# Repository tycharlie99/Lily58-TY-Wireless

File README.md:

# TsunyYu - Lily58

An ergonomic, split mechanical keyboard with a 58-key columnar-staggered layout, derived from the original [Lily58](https://github.com/kata0510/Lily58). This specific variant is optimized for wireless dual-mode connectivity and ultra-low-power Nice!View displays, perfect for developers and creators seeking a clean, cable-free workspace.

## Features

- **Ergonomic Columnar Layout**: 4x12 matrix with 5 thumb keys per side (58 keys total) reduces finger travel and hand strain.
- **Wireless-Ready**: Integrated battery support for seamless Bluetooth operation when paired with BLE controllers (e.g., nice!nano).
- **Nice!View Optimization**: Native compatibility with the low-power Sharp Memory Display (Nice!View), offering a high refresh rate with a fraction of the power consumption of traditional OLEDs.
- **Reversible PCB Design**: Uses a mirrored, flippable design for the left and right sides to simplify manufacturing and sourcing.
---

## Bill of Materials (BOM)

Below is the complete list of components required to build one full TsunyYu - Lily58 keyboard (including both left and right halves):

| Item | Quantity | Model/Specification / Notes |
| --- | --- | --- |
| **Lily58 PCB** | 2 | Left and right halves (reversible design) |
| **PCB Plate** | 2 | Left and right halves (compatible with 58-key layout) |
| **Microcontroller** | 2 | Pro Micro or compatible BLE wireless controllers (e.g., nice!nano) |
| **Display** | 2 | Nice!View (Ultra-low-power display; backward compatible with 0.91" OLED) |
| **Key Socket** | 58 | Kailh Hotswap Sockets |
| **Switches** | 58 | MX switches |
| **Keycaps** | 58 | 1U keycaps recommended, 1.5U optional for thumb keys |
| **Diodes** | 58 | 1N4148W (SOD-123) |
| **Resistors** | 4 | 4k7 ohm (0603) Used for I2C/Display signal stability |
| **TRRS Jack** | 2 | PJ-320A or equivalent (for wired connection between halves) |
| **Batteries** | 2 | 3.7V Li-Po batteries (Required for wireless; 110mAh to 300mAh recommended) |
| **Battery Holders** | 2 | JST GH 1.25mm 2p |
| **Reset Buttons** | 2 | KXT 321 |

---

## Hardware & Soldering Guide

Please review these critical steps before heating up your soldering iron:

1. **Orientation Check**: Because the PCB is reversible, make sure you clearly identify the "Left" and "Right" sides before soldering any components. Do not accidentally mirror the components on the same side.
2. **Diode Polarity**: Diodes are directional. Ensure the line on the diode (cathode) aligns with the thick line/bar indicated on the PCB silkscreen markings.
3. **Wireless Safety Precautions**:
   - Always unplug the battery from the **JST GH connector** before soldering/desoldering any components nearby to prevent accidental short circuits.
   - It is highly recommended to apply **insulating tape** (like Kapton tape) over the PCB traces beneath the microcontroller to prevent shorts between the controller pins and the PCB components/battery.
   - Pay close attention to the pinout when installing the Nice!View. It requires 5 pins (including a CS pin), differing slightly from standard 4-pin OLED setups.

---

## Firmware Support

This build is fully compatible with open-source keyboard firmwares:

- **ZMK Firmware (Highly Recommended)**: The ideal choice when paired with nice!nano controllers. It natively handles Bluetooth multi-device pairing and unlocks the full low-power efficiency of the Nice!View screen.
- **QMK Firmware**: Best suited for standard wired setups using traditional Pro Micro controllers.

---

## References & Credits

This project is built upon and inspired by the incredible open-source work of the mechanical keyboard community:

- [kata0510/Lily58](https://github.com/kata0510/Lily58) - The original Lily58 design.
- [ZMK Firmware](https://zmk.dev/) & [nice!nano](https://nicekeyboards.com/) - Providing the robust ecosystem for wireless split keyboards.

---

## License

This hardware project is open-source and distributed under the same licensing terms as the original repository:
- **Distributed under the [MIT License](LICENSE)** *(Or specify CERN OHL if applicable to your custom PCB modifications).*

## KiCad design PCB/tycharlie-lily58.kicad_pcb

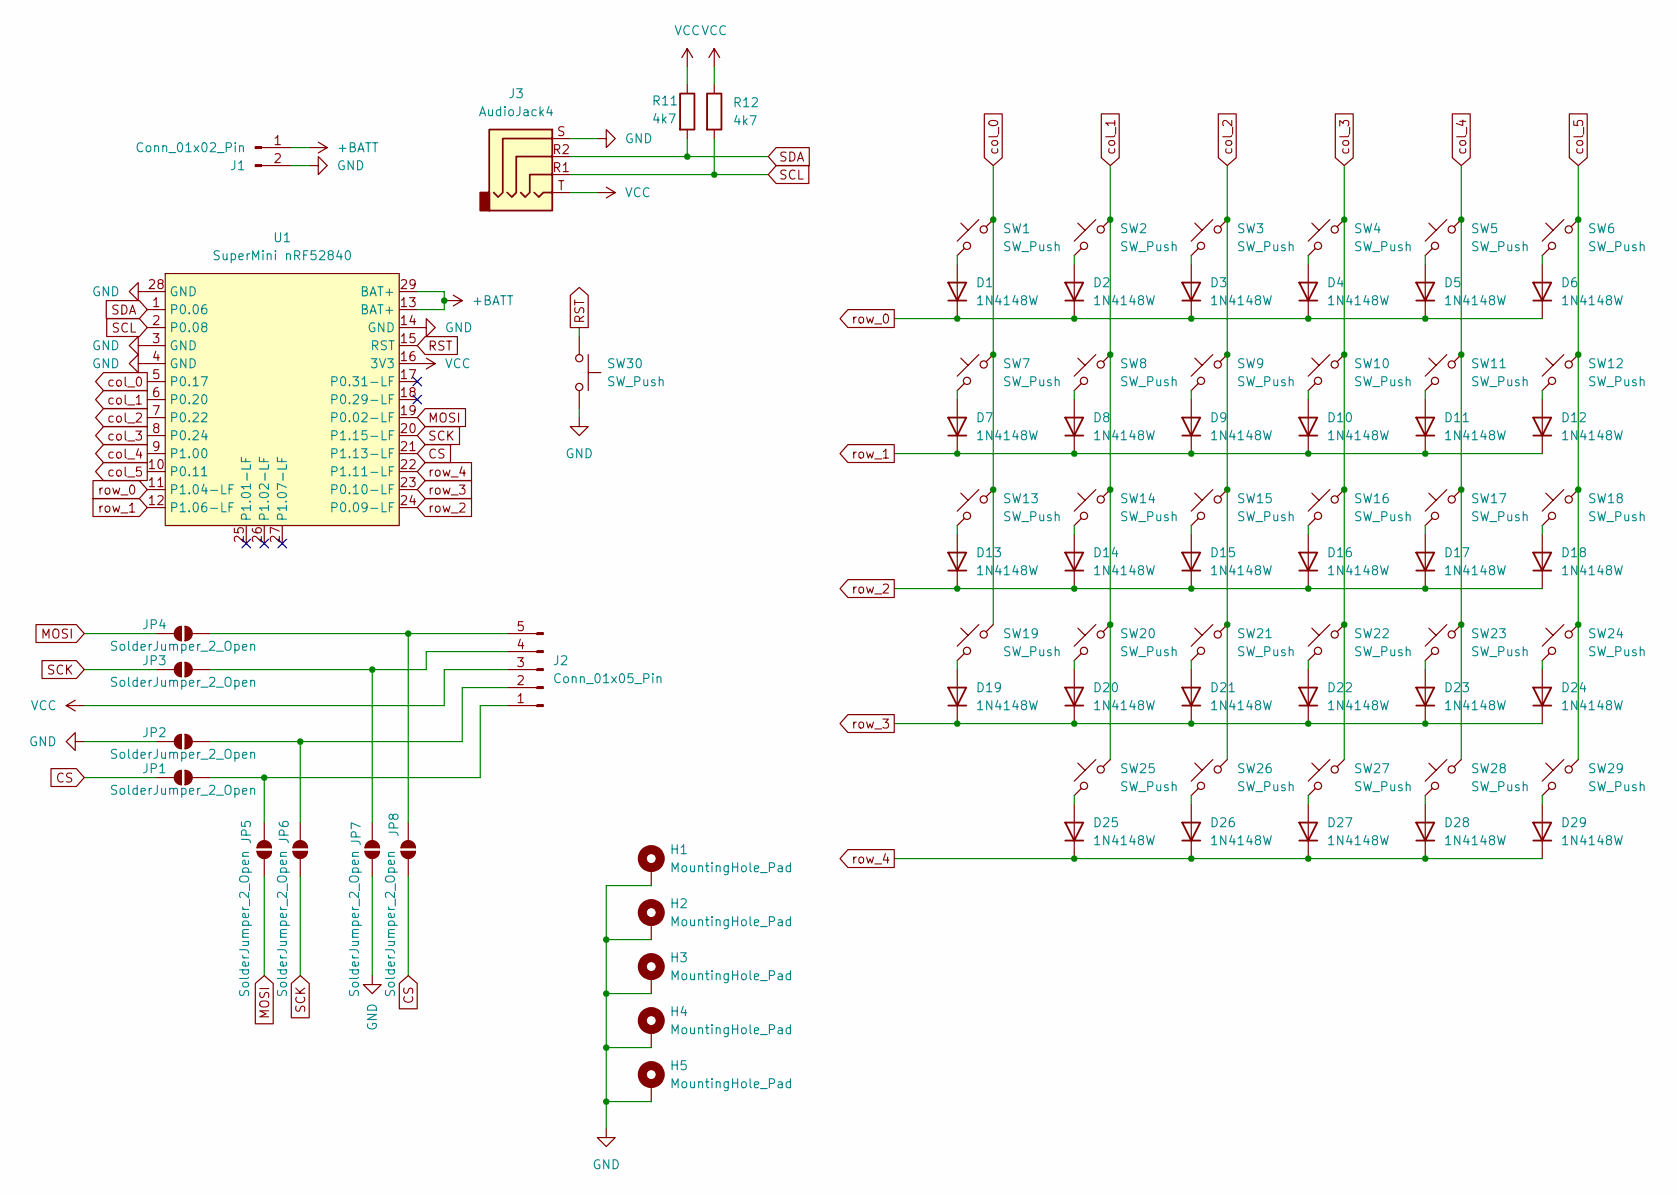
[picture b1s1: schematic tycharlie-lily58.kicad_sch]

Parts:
D1, D2, D3, D4, D5, D6, D7, D8, D9, D10, D11, D12, D13, D14, D15, D16, D17, D18, D19, D20, D21, D22, D23, D24, D25, D26, D27, D28, D29: 1N4148W; D_SOD-123
H1, H2, H4: MountingHole_Pad; MountingHole_3mm_Oval_Hole_ISO14580_Pad_TopBottom
H3: MountingHole_Pad; MountingHole_2.2mm_M2_ISO14580_Pad_TopBottom
H5: MountingHole_Pad; MountingHole_3mm_M2_ISO14580_Pad_TopBottom
J1: Conn_01x02_Pin; Molex_PicoBlade_53261-0271_1x02-1MP_P1.25mm_Horizontal
J2: Conn_01x05_Pin; PinHeader_1x05_P2.54mm_Vertical
J3: AudioJack4; CON_MJ-4PP-9_Reversible
JP1, JP2, JP3, JP4, JP5, JP6, JP7, JP8: SolderJumper_2_Open; SolderJumper-2_P1.3mm_Open_RoundedPad1.0x1.5mm
R11, R12: 4k7; R_0603_1608Metric_Pad0.98x0.95mm_HandSolder
SW1, SW2, SW3, SW4, SW5, SW6, SW7, SW8, SW9, SW10, SW11, SW12, SW13, SW14, SW15, SW16, SW17, SW18, SW19, SW20, SW21, SW22, SW23, SW24, SW25, SW26, SW27, SW29: SW_Push; SW_Hotswap_Reversible_Kailh_MX_Plated_1.00u
SW28: SW_Push; SW_Hotswap_Reversible_Kailh_MX_Plated_1.50u
SW30: SW_Push; SW_SPST_CK_KXT3
U1: SuperMini nRF52840; SuperMini_nRF52840_without_25-27

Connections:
+BATT: J1.1, U1.13 (BAT+), U1.29 (BAT+)
CS: JP1.1 (A), JP8.1 (A), U1.21 (P1.13-LF)
GND: H1.1 (1_1), H2.1 (1_1), H3.1 (1_1), H4.1 (1_1), H5.1 (1_1), J1.2, J3.S, JP2.1 (A), JP7.1 (A), SW30.2, U1.3 (GND), U1.4 (GND), U1.14 (GND), U1.28 (GND)
MOSI: JP4.1 (A), JP5.1 (A), U1.19 (P0.02-LF)
unnamed: D1.2 (A), SW1.1
unnamed: D2.2 (A), SW2.1
unnamed: D3.2 (A), SW3.1
unnamed: D4.2 (A), SW4.1
unnamed: D5.2 (A), SW5.1
unnamed: D6.2 (A), SW6.1
unnamed: D7.2 (A), SW7.1
unnamed: D8.2 (A), SW8.1
unnamed: D9.2 (A), SW9.1
unnamed: D10.2 (A), SW10.1
unnamed: D11.2 (A), SW11.1
unnamed: D12.2 (A), SW12.1
unnamed: D13.2 (A), SW13.1
unnamed: D14.2 (A), SW14.1
unnamed: D15.2 (A), SW15.1
unnamed: D16.2 (A), SW16.1
unnamed: D17.2 (A), SW17.1
unnamed: D18.2 (A), SW18.1
unnamed: D19.2 (A), SW19.1
unnamed: D20.2 (A), SW20.1
unnamed: D21.2 (A), SW21.1
unnamed: D22.2 (A), SW22.1
unnamed: D23.2 (A), SW23.1
unnamed: D24.2 (A), SW24.1
unnamed: D25.2 (A), SW25.1
unnamed: D26.2 (A), SW26.1
unnamed: D27.2 (A), SW27.1
unnamed: D28.2 (A), SW28.1
unnamed: D29.2 (A), SW29.1
unnamed: J2.1, JP1.2 (B), JP5.2 (B)
unnamed: J2.2, JP2.2 (B), JP6.2 (B)
unnamed: J2.4, JP3.2 (B), JP7.2 (B)
unnamed: J2.5, JP4.2 (B), JP8.2 (B)
RST: SW30.1, U1.15 (RST)
SCK: JP3.1 (A), JP6.1 (A), U1.20 (P1.15-LF)
SCL: J3.R1, R12.2, U1.2 (P0.08)
SDA: J3.R2, R11.2, U1.1 (P0.06)
VCC: J2.3, J3.T, R11.1, R12.1, U1.16 (3V3)
col_0: SW1.2, SW7.2, SW13.2, SW19.2, U1.5 (P0.17)
col_1: SW2.2, SW8.2, SW14.2, SW20.2, SW25.2, U1.6 (P0.20)
col_2: SW3.2, SW9.2, SW15.2, SW21.2, SW26.2, U1.7 (P0.22)
col_3: SW4.2, SW10.2, SW16.2, SW22.2, SW27.2, U1.8 (P0.24)
col_4: SW5.2, SW11.2, SW17.2, SW23.2, SW28.2, U1.9 (P1.00)
col_5: SW6.2, SW12.2, SW18.2, SW24.2, SW29.2, U1.10 (P0.11)
row_0: D1.1 (K), D2.1 (K), D3.1 (K), D4.1 (K), D5.1 (K), D6.1 (K), U1.11 (P1.04-LF)
row_1: D7.1 (K), D8.1 (K), D9.1 (K), D10.1 (K), D11.1 (K), D12.1 (K), U1.12 (P1.06-LF)
row_2: D13.1 (K), D14.1 (K), D15.1 (K), D16.1 (K), D17.1 (K), D18.1 (K), U1.24 (P0.09-LF)
row_3: D19.1 (K), D20.1 (K), D21.1 (K), D22.1 (K), D23.1 (K), D24.1 (K), U1.23 (P0.10-LF)
row_4: D25.1 (K), D26.1 (K), D27.1 (K), D28.1 (K), D29.1 (K), U1.22 (P1.11-LF)

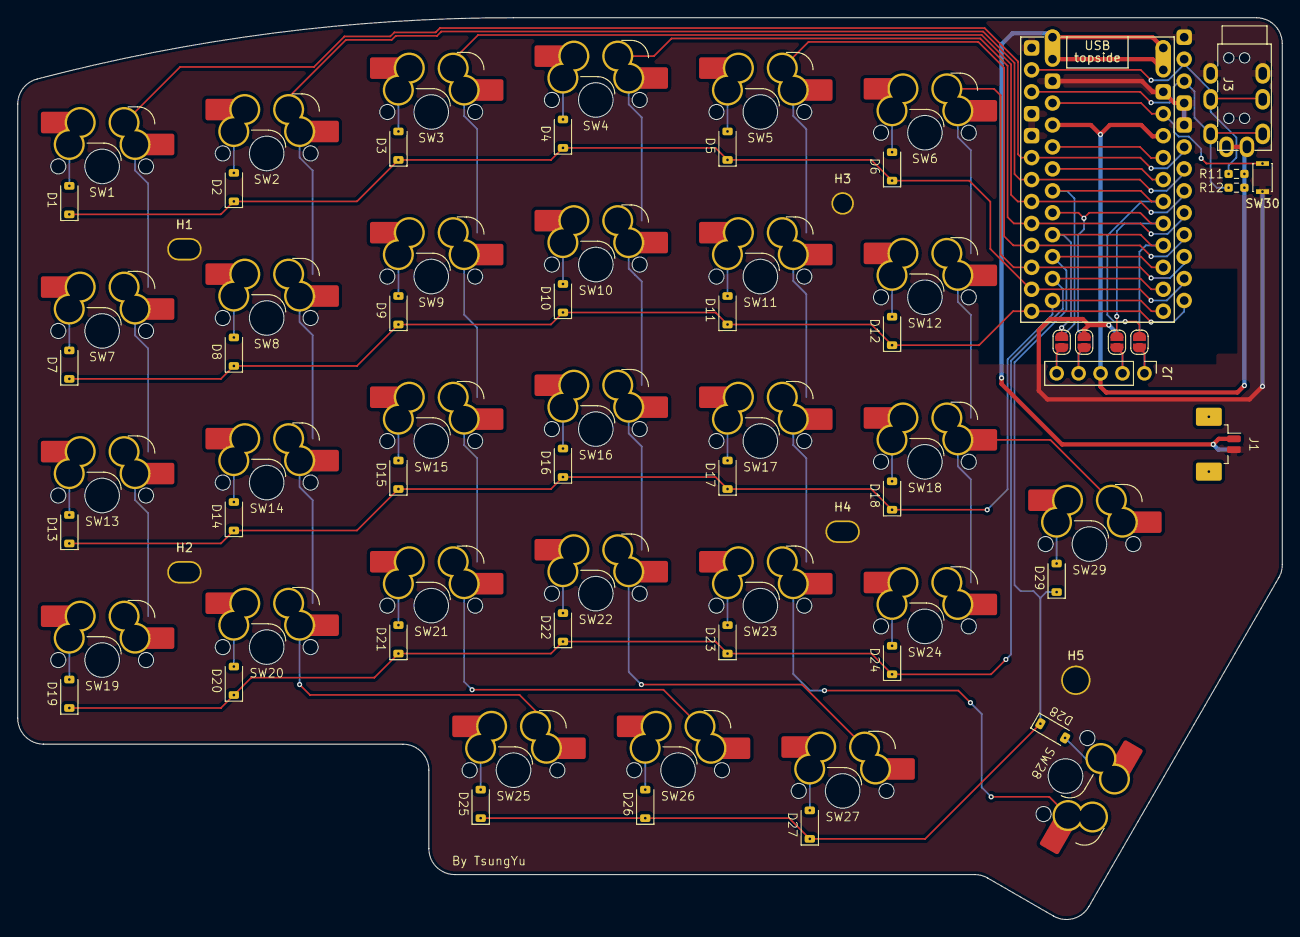
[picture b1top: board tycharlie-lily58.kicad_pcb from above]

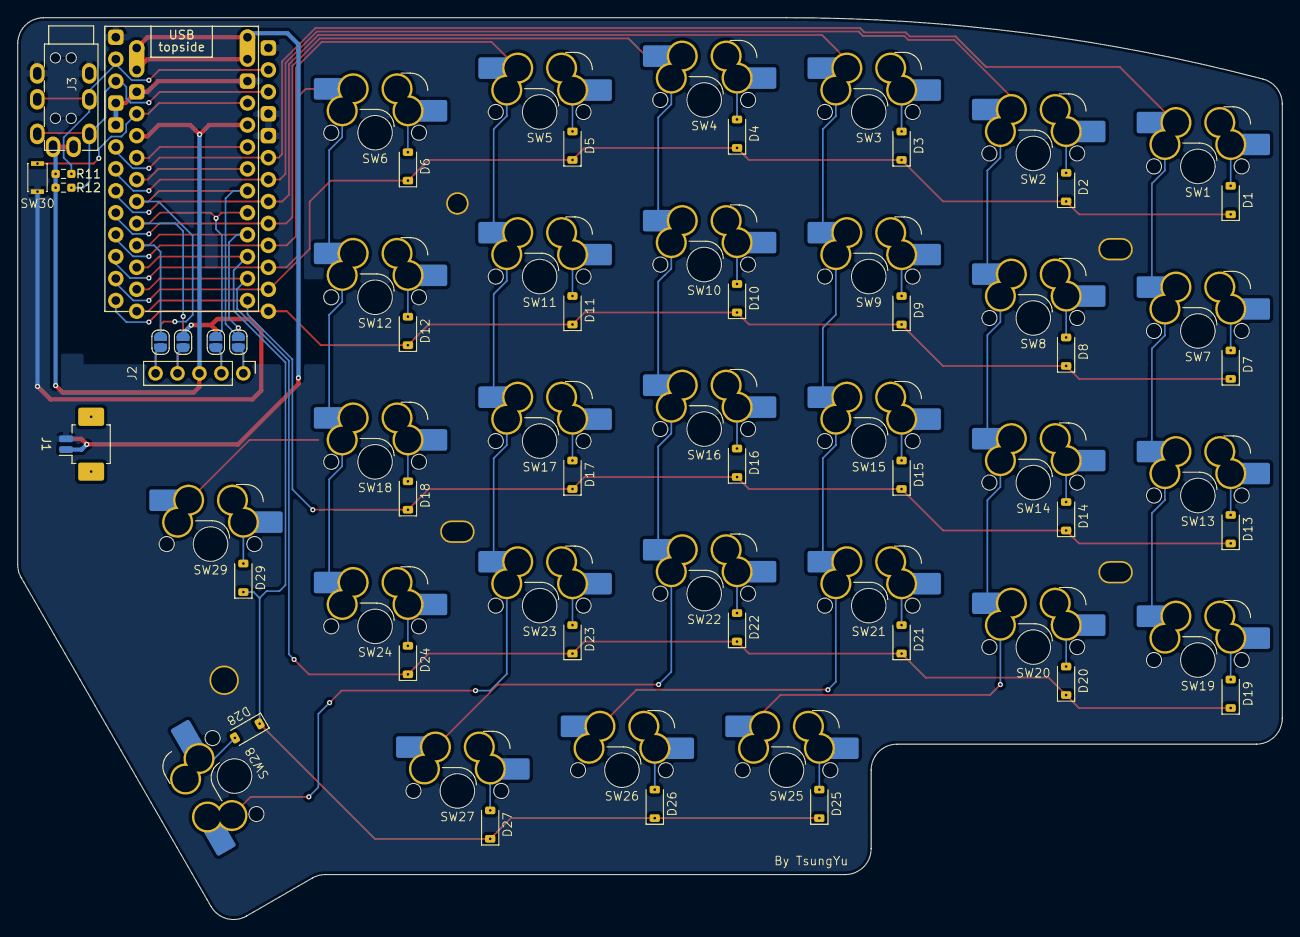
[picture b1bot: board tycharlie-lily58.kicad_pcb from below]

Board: 2 copper layers, 146.4 x 104.4 mm, 78 parts (36 on the bottom side), 53 nets.

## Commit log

2026-05-23 FEAT: add the pcb data finish the schematic design and the pcb layout
2026-05-23 FEAT: add the dxf file for edge cut - use the dxf file to maintain the edge cut - add two different mounting hole - use larger mounting hole for robustness
2026-05-23 FIX: fix the group issue the group item in the pcb will not correctly when using the different version, regroup them
2026-05-23 FEAT: add the keyboard plate
2026-05-24 FIX: update the plate mounting hole size
2026-06-07 CHORE: add the name on pcb
2026-06-07 FEAT: add the zmk config
2026-06-07 FEAT: enable zmk studio
2026-06-07 FEAT: add for win/mac layer
2026-06-07 FEAT: update the keymap
    - add the lower/raise layer
2026-06-07 FIX: update the battery footprint
    - Add new Molex PicoBlade 53261 foorprint
    - Changed the battery pin1 to BATT+
2026-06-07 FEAT: add two layers
2026-06-07 FEAT: add the nice view
2026-06-07 FEAT: add the README
2026-06-07 FIX: keymap LAYER name typo
2026-06-07 FEAT: update keymap
    - update the lower/raise
    - redesign the keymap
2026-06-07 FEAT: disable studio lock
2026-06-10 FEAT: add sleep key and auto sleep
    - add the sleep to raise layer
    - enable the auto sleep
2026-06-10 FEAT: disable the wpm display
2026-06-13 FEAT: update plate mounting hole size
    - change the mounting hole to 5mm
    - renamed the mounting hole footprint name
